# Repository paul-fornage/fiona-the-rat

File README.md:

### Fiona

# WIP
Only public to save progress at the expense of microsoft

KiCad Repo

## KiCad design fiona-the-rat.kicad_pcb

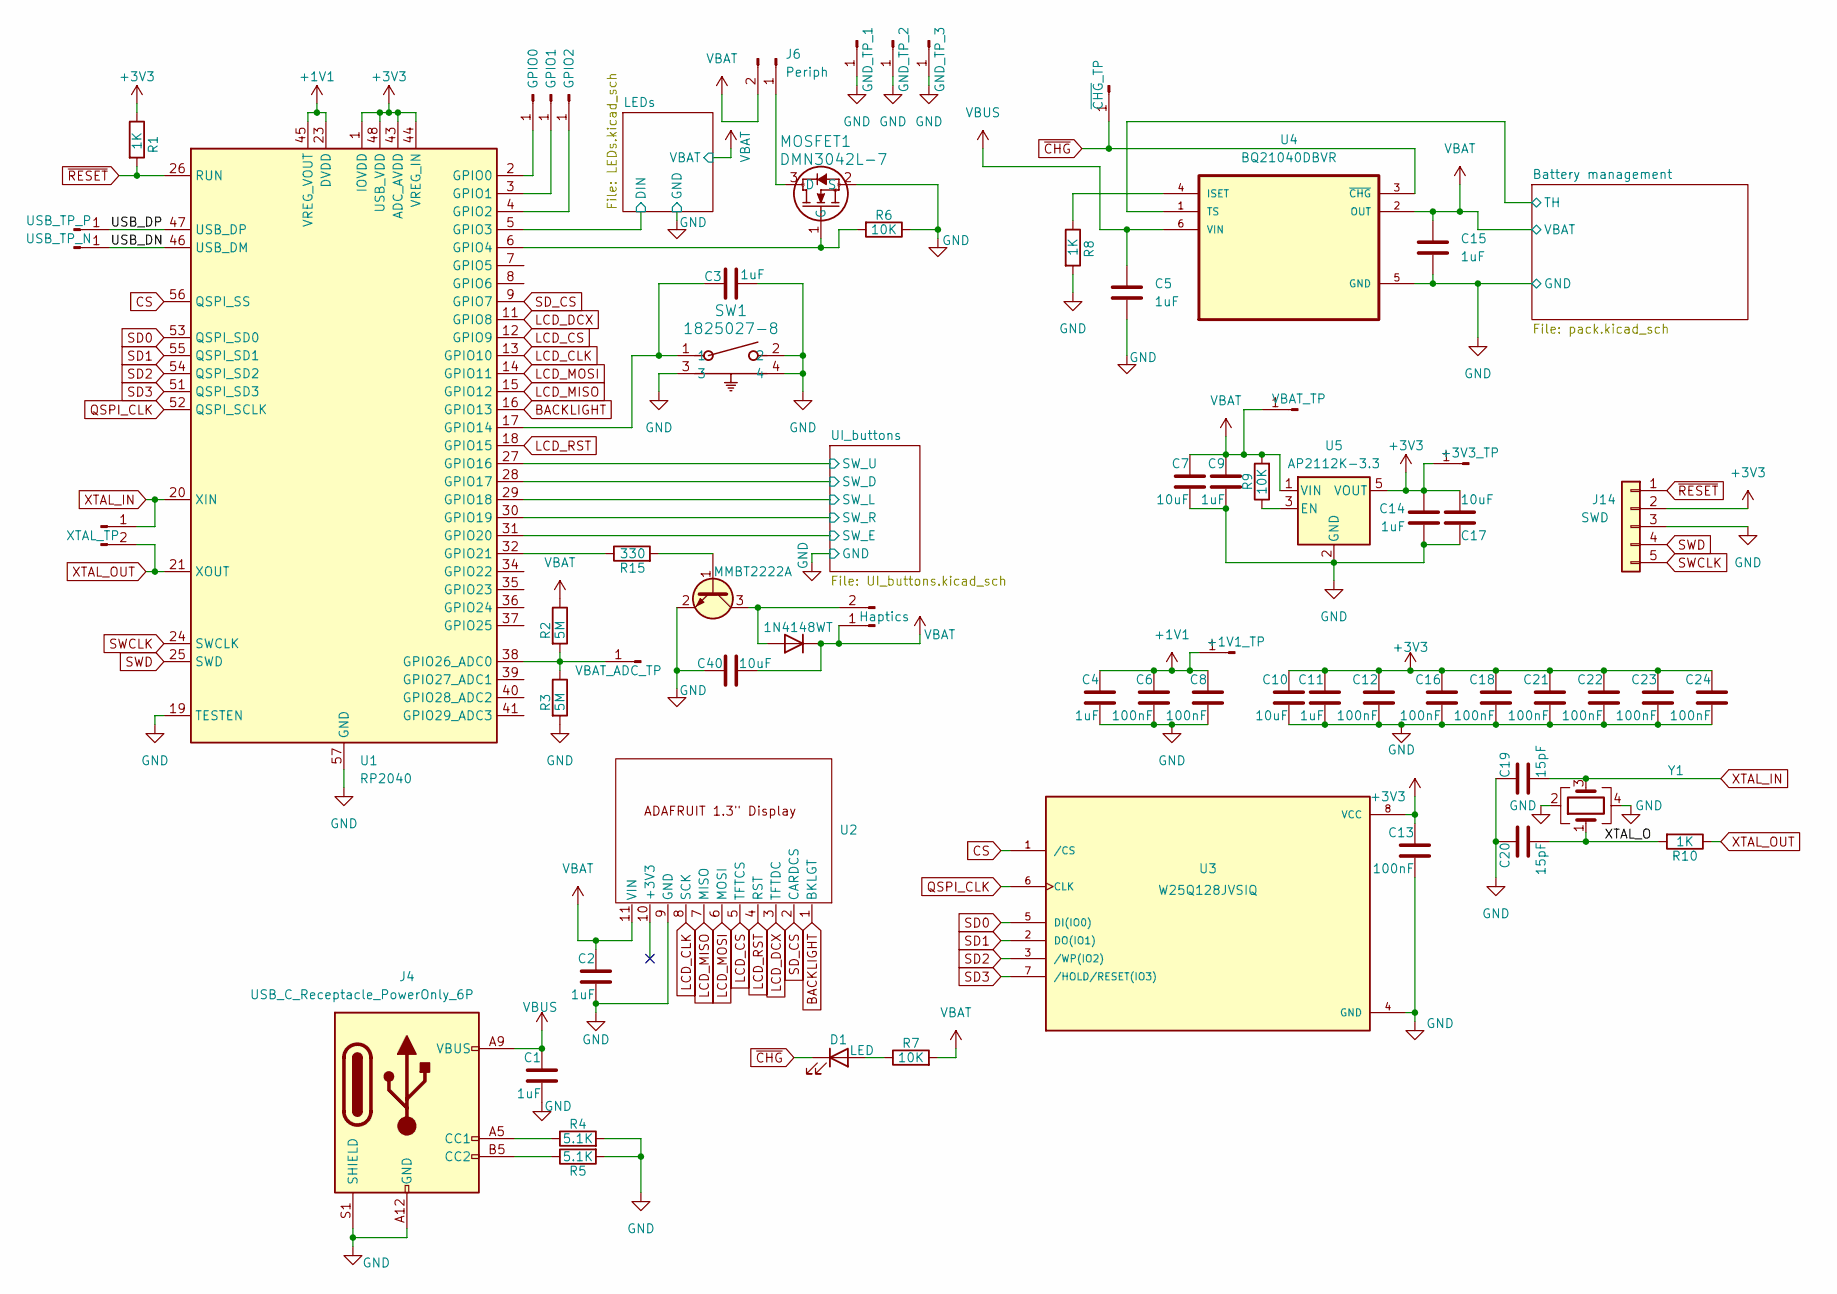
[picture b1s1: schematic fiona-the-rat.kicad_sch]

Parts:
C1, C2, C3, C4, C5, C9, C11, C14, C15: 1uF; C_0603_1608Metric
C6, C8, C12, C13, C16, C18, C21, C22, C23, C24: 100nF; C_0603_1608Metric
C7, C10, C17, C40: 10uF; C_0603_1608Metric
C19, C20: 15pF; C_0603_1608Metric
D1: LED; LED_0603_1608Metric
D2: 1N4148WT; D_SOD-523
J1: USB_TP_P; PinHeader_1x01_P2.54mm_Vertical
J2: USB_TP_N; PinHeader_1x01_P2.54mm_Vertical
J3: XTAL_TP; PinSocket_1x02_P2.54mm_Vertical
J4: USB_C_Receptacle_PowerOnly_6P; USB_C_Receptacle_GCT_USB4125-xx-x_6P_TopMnt_Horizontal
J5: VBAT_ADC_TP; PinHeader_1x01_P2.54mm_Vertical
J6: Periph; JST_XH_B2B-XH-A_1x02_P2.50mm_Vertical
J7: GND_TP_1; PinHeader_1x01_P2.54mm_Vertical
J8: GND_TP_2; PinHeader_1x01_P2.54mm_Vertical
J9: GND_TP_3; PinHeader_1x01_P2.54mm_Vertical
J10: ~{CHG}_TP; PinHeader_1x01_P2.54mm_Vertical
J11: +1V1_TP; PinHeader_1x01_P2.54mm_Vertical
J12: VBAT_TP; PinHeader_1x01_P2.54mm_Vertical
J13: +3V3_TP; PinHeader_1x01_P2.54mm_Vertical
J14: SWD; PinSocket_1x05_P2.54mm_Vertical
J19: GPIO0; PinHeader_1x01_P2.54mm_Vertical
J20: GPIO1; PinHeader_1x01_P2.54mm_Vertical
J21: GPIO2; PinHeader_1x01_P2.54mm_Vertical
J22: Haptics; JST_XH_B2B-XH-A_1x02_P2.50mm_Vertical
MOSFET1: DMN3042L-7; SOT23_DMN3042L_DIO
Q1: MMBT2222A; SOT-23
R1, R8, R10: 1K; R_0603_1608Metric
R2, R3: 5M; R_0603_1608Metric
R4, R5: 5.1K; R_0603_1608Metric
R6, R7, R9: 10K; R_0603_1608Metric
R15: 330; R_0603_1608Metric
SW1: 1825027-8; SW2_1825027-C_TEC
U1: RP2040; QFN-56-1EP_7x7mm_P0.4mm_EP3.2x3.2mm
U2: adafruit-4313-display
U3: W25Q128JVSIQ; SOIC127P790X216-8N; PARTREV I
U4: BQ21040DBVR; SOT95P280X145-6N
U5: AP2112K-3.3; SOT-23-5
Y1: Crystal_GND24; Crystal_SMD_Abracon_ABM8G-4Pin_3.2x2.5mm

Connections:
+1V1: C4.1, C6.1, C8.1, J11.1, U1.23 (DVDD), U1.45 (VREG_VOUT), U1.50 (DVDD)
+3V3: C10.1, C11.1, C12.1, C13.1, C14.1, C16.1, C17.2, C18.1, C21.1, C22.1, C23.1, C24.1, J13.1, J14.2, R1.1, U1.1 (IOVDD), U1.10 (IOVDD), U1.22 (IOVDD), U1.33 (IOVDD), U1.42 (IOVDD), U1.43 (ADC_AVDD), U1.44 (VREG_IN), U1.48 (USB_VDD), U1.49 (IOVDD), U3.8 (VCC), U5.5 (VOUT)
/Battery management/TH: U4.1 (TS); also elsewhere on the board
/LEDs/DIN: U1.5 (GPIO3); also elsewhere on the board
/UI_buttons/SW_D: U1.28 (GPIO17); also elsewhere on the board
/UI_buttons/SW_E: U1.31 (GPIO20); also elsewhere on the board
/UI_buttons/SW_L: U1.29 (GPIO18); also elsewhere on the board
/UI_buttons/SW_R: U1.30 (GPIO19); also elsewhere on the board
/UI_buttons/SW_U: U1.27 (GPIO16); also elsewhere on the board
/USB_DN: J2.1, U1.46 (USB_DM)
/USB_DP: J1.1, U1.47 (USB_DP)
/XTAL_O: C20.2, R10.2, Y1.1; also elsewhere on the board
BACKLIGHT: U1.16 (GPIO13), U2.1 (BKLGT)
CS: U1.56 (QSPI_SS), U3.1 (/CS)
GND: C1.2, C2.2, C3.2, C4.2, C5.2, C6.2, C7.2, C8.2, C9.2, C10.2, C11.2, C12.2, C13.2, C14.2, C15.2, C16.2, C17.1, C18.2, C19.1, C20.1, C21.2, C22.2, C23.2, C24.2, C40.1, J4.A12 (GND), J4.B12 (GND), J4.S1 (SHIELD), J7.1, J8.1, J9.1, J14.3, MOSFET1.2 (S), Q1.2 (E), R3.2, R4.2, R5.2, R6.1, R8.2, SW1.2, SW1.3, SW1.4, U1.19 (TESTEN), U1.57 (GND), U2.9 (GND), U3.4 (GND), U4.5 (GND), U5.2 (GND), Y1.2, Y1.4; also elsewhere on the board
LCD_CLK: U1.13 (GPIO10), U2.8 (SCK)
LCD_CS: U1.12 (GPIO9), U2.5 (TFTCS)
LCD_DCX: U1.11 (GPIO8), U2.3 (TFTDC)
LCD_MISO: U1.15 (GPIO12), U2.7 (MISO)
LCD_MOSI: U1.14 (GPIO11), U2.6 (MOSI)
LCD_RST: U1.18 (GPIO15), U2.4 (RST)
unnamed: D1.2 (A), R7.1
unnamed: D2.2 (A), J22.2, Q1.3 (C)
unnamed: J4.A5 (CC1), R4.1
unnamed: J4.B5 (CC2), R5.1
unnamed: J5.1, R2.2, R3.1, U1.38 (GPIO26_ADC0)
unnamed: J6.1, MOSFET1.3 (D)
unnamed: J19.1, U1.2 (GPIO0)
unnamed: J20.1, U1.3 (GPIO1)
unnamed: J21.1, U1.4 (GPIO2)
unnamed: MOSFET1.1 (G), R6.2, U1.6 (GPIO4)
unnamed: Q1.1 (B), R15.2
unnamed: C3.1, SW1.1, U1.17 (GPIO14)
unnamed: R15.1, U1.32 (GPIO21)
unnamed: R8.1, U4.4 (ISET)
unnamed: R9.1, U5.3 (EN)
QSPI_CLK: U1.52 (QSPI_SCLK), U3.6 (CLK)
SD0: U1.53 (QSPI_SD0), U3.5 (DI(IO0))
SD1: U1.55 (QSPI_SD1), U3.2 (DO(IO1))
SD2: U1.54 (QSPI_SD2), U3.3 (/WP(IO2))
SD3: U1.51 (QSPI_SD3), U3.7 (/HOLD/RESET(IO3))
SD_CS: U1.9 (GPIO7), U2.2 (CARDCS)
SWCLK: J14.5, U1.24 (SWCLK)
SWD: J14.4, U1.25 (SWD)
VBAT: C2.1, C7.1, C9.1, C15.1, C40.2, D2.1 (K), J6.2, J12.1, J22.1, R2.1, R7.2, R9.2, U2.11 (VIN), U4.2 (OUT), U5.1 (VIN); also elsewhere on the board
VBUS: C1.1, C5.1, J4.A9 (VBUS), J4.B9 (VBUS), U4.6 (VIN)
XTAL_IN: C19.2, J3.1, U1.20 (XIN), Y1.3; also elsewhere on the board
XTAL_OUT: J3.2, R10.1, U1.21 (XOUT)
~CHG: D1.1 (K), J10.1, U4.3 (~CHG)
~RESET: J14.1, R1.2, U1.26 (RUN)

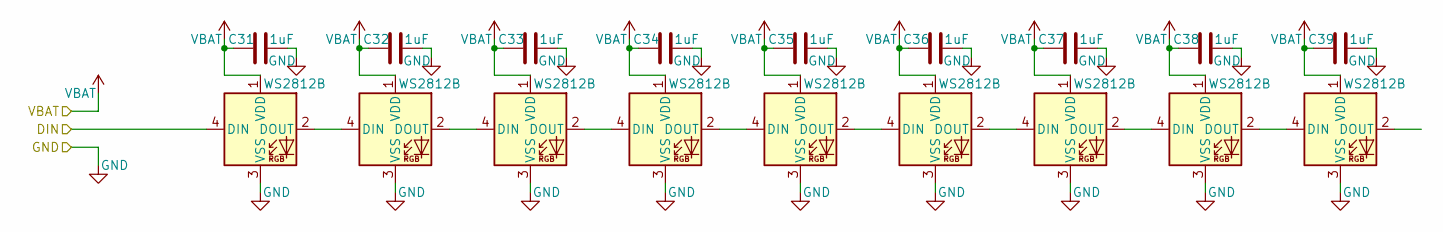
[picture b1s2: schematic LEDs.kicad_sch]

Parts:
C31, C32, C33, C34, C35, C36, C37, C38, C39: 1uF; C_0603_1608Metric
WLED1, WLED2, WLED3, WLED4, WLED5, WLED6, WLED7, WLED8, WLED9: WS2812B; LED_WS2812B_PLCC4_5.0x5.0mm_P3.2mm

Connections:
/LEDs/DIN: WLED1.4 (DIN); also elsewhere on the board
GND: C31.2, C32.2, C33.2, C34.2, C35.2, C36.2, C37.2, C38.2, C39.2, WLED1.3 (VSS), WLED2.3 (VSS), WLED3.3 (VSS), WLED4.3 (VSS), WLED5.3 (VSS), WLED6.3 (VSS), WLED7.3 (VSS), WLED8.3 (VSS), WLED9.3 (VSS); also elsewhere on the board
unnamed: WLED1.2 (DOUT), WLED2.4 (DIN)
unnamed: WLED2.2 (DOUT), WLED3.4 (DIN)
unnamed: WLED3.2 (DOUT), WLED4.4 (DIN)
unnamed: WLED4.2 (DOUT), WLED5.4 (DIN)
unnamed: WLED5.2 (DOUT), WLED6.4 (DIN)
unnamed: WLED6.2 (DOUT), WLED7.4 (DIN)
unnamed: WLED7.2 (DOUT), WLED8.4 (DIN)
unnamed: WLED8.2 (DOUT), WLED9.4 (DIN)
VBAT: C31.1, C32.1, C33.1, C34.1, C35.1, C36.1, C37.1, C38.1, C39.1, WLED1.1 (VDD), WLED2.1 (VDD), WLED3.1 (VDD), WLED4.1 (VDD), WLED5.1 (VDD), WLED6.1 (VDD), WLED7.1 (VDD), WLED8.1 (VDD), WLED9.1 (VDD); also elsewhere on the board

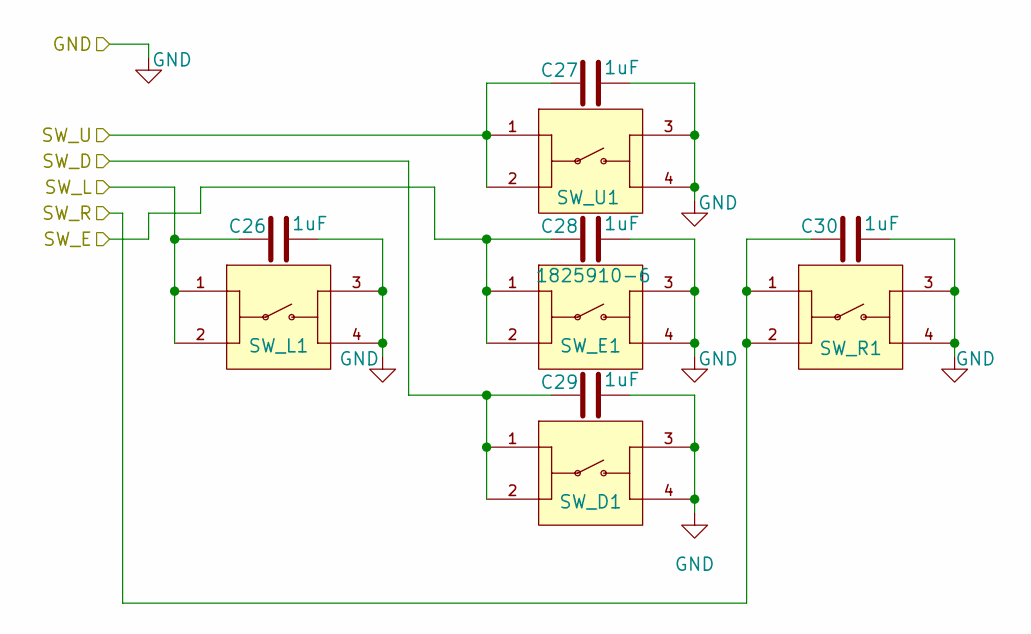
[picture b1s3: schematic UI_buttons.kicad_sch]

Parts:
C26, C27, C28, C29, C30: 1uF; C_0603_1608Metric
SW_D1: 1825910-6; SW_1825910-6-4; PARTREV C10
SW_E1: 1825910-6; SW_1825910-6-4; PARTREV C10
SW_L1: 1825910-6; SW_1825910-6-4; PARTREV C10
SW_R1: 1825910-6; SW_1825910-6-4; PARTREV C10
SW_U1: 1825910-6; SW_1825910-6-4; PARTREV C10

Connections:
/UI_buttons/SW_D: C29.1, SW_D1.1, SW_D1.2; also elsewhere on the board
/UI_buttons/SW_E: C28.1, SW_E1.1, SW_E1.2; also elsewhere on the board
/UI_buttons/SW_L: C26.1, SW_L1.1, SW_L1.2; also elsewhere on the board
/UI_buttons/SW_R: C30.1, SW_R1.1, SW_R1.2; also elsewhere on the board
/UI_buttons/SW_U: C27.1, SW_U1.1, SW_U1.2; also elsewhere on the board
GND: C26.2, C27.2, C28.2, C29.2, C30.2, SW_D1.3, SW_D1.4, SW_E1.3, SW_E1.4, SW_L1.3, SW_L1.4, SW_R1.3, SW_R1.4, SW_U1.3, SW_U1.4; also elsewhere on the board

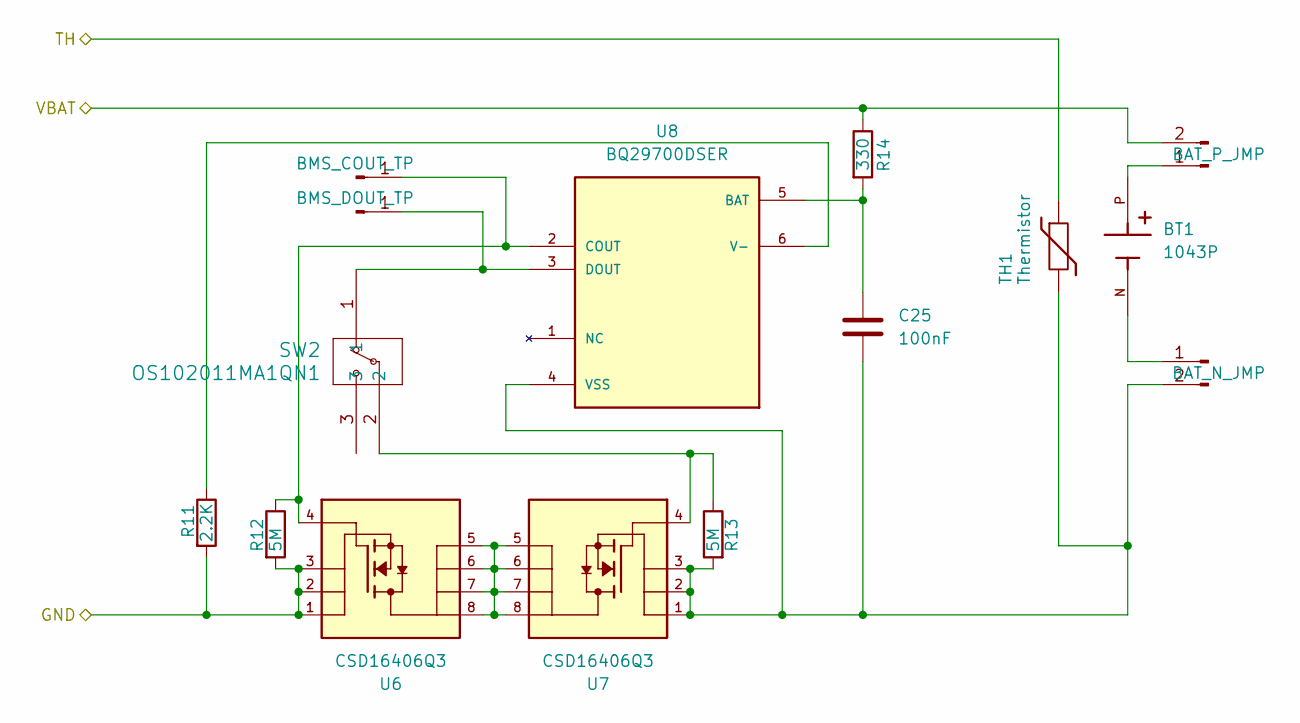
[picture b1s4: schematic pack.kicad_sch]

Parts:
BT1: 1043P; BAT_1043P; PARTREV D
C25: 100nF; C_0603_1608Metric
J15: BMS_COUT_TP; PinHeader_1x01_P2.54mm_Vertical
J16: BMS_DOUT_TP; PinHeader_1x01_P2.54mm_Vertical
J17: BAT_P_JMP; PinSocket_1x02_P2.54mm_Vertical
J18: BAT_N_JMP; PinSocket_1x02_P2.54mm_Vertical
R11: 2.2K; R_0603_1608Metric
R12, R13: 5M; R_0603_1608Metric
R14: 330; R_0603_1608Metric
SW2: OS102011MA1QN1; OS102011MA1QN1_CNK
TH1: Thermistor; R_0402_1005Metric
U6, U7: CSD16406Q3; TRANS_CSD16406Q3
U8: BQ29700DSER; SON50P150X150X80-6N; PARTREV G

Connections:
/Battery management/TH: TH1.1; also elsewhere on the board
GND: R11.2, R12.2, U6.1, U6.2, U6.3; also elsewhere on the board
unnamed: J15.1, R12.1, U6.4, U8.2 (COUT)
unnamed: J16.1, SW2.1, U8.3 (DOUT)
unnamed: BT1.P, J17.1
unnamed: BT1.N, J18.1
unnamed: C25.1, J18.2, R13.2, TH1.2, U7.1, U7.2, U7.3, U8.4 (VSS)
unnamed: R13.1, SW2.2, U7.4
unnamed: U6.5, U6.6, U6.7, U6.8, U7.5, U7.6, U7.7, U7.8
unnamed: C25.2, R14.2, U8.5 (BAT)
unnamed: R11.1, U8.6 (V-)
VBAT: J17.2, R14.1; also elsewhere on the board

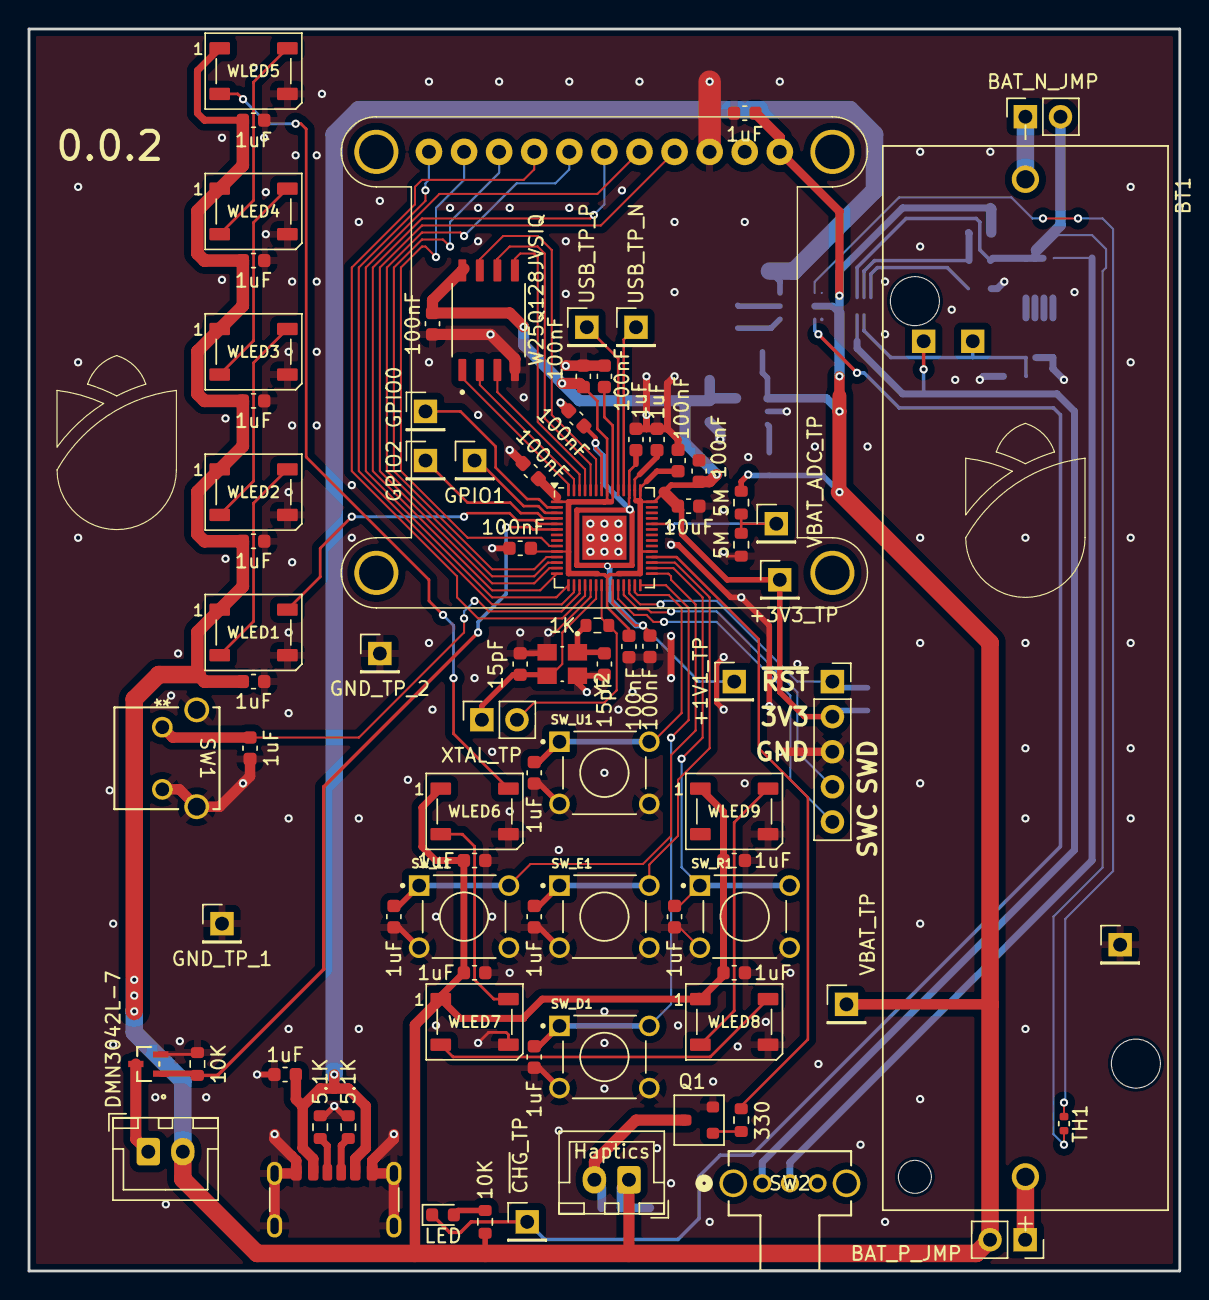
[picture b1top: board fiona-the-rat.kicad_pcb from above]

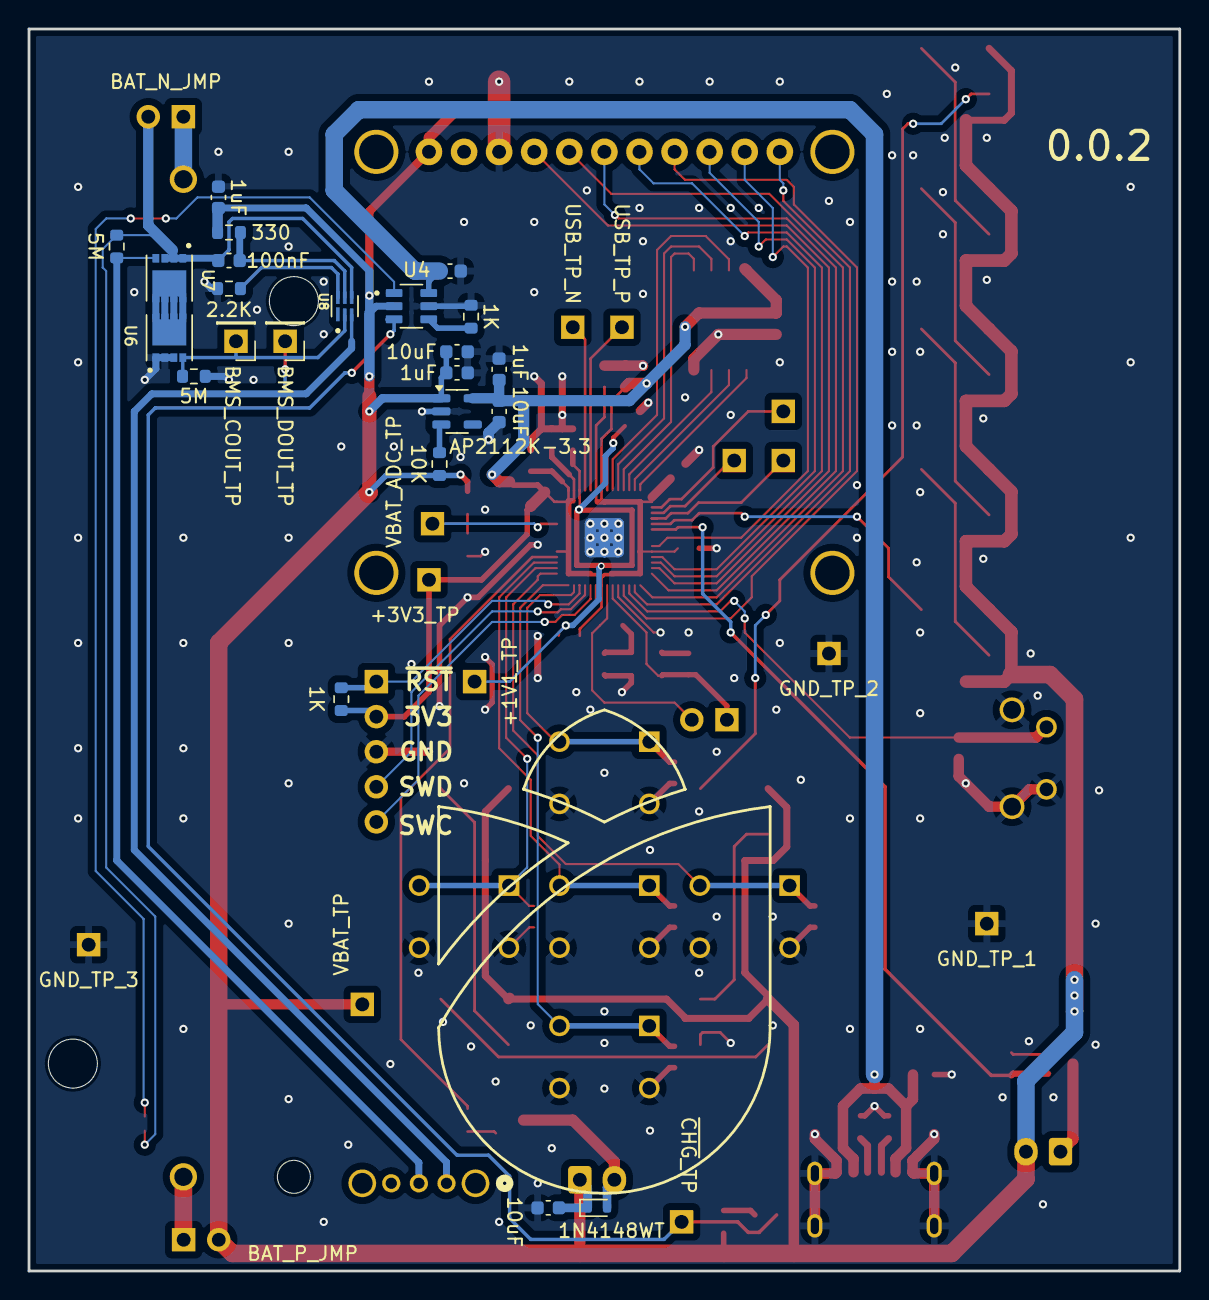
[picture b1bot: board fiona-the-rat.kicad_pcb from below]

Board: 2 copper layers, 83.3 x 89.9 mm, 108 parts (23 on the bottom side), 67 nets.

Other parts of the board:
Y2: ABM8G-12.000MHZ-18-D2Y-T; XTAL_ABM8G-12.000MHZ-18-D2Y-T

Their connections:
/XTAL_O: Y2.1; also elsewhere on the board
GND: Y2.2 (GND), Y2.4 (GND); also elsewhere on the board
XTAL_IN: Y2.3; also elsewhere on the board

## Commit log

2025-07-10 init
    just saving work, not finished
2025-07-10 working on stuff
2025-07-11 Forgor MD
2025-07-11 placed all components
2025-07-11 adding stuff
2025-07-11 tweaking
2025-07-11 0.0.1 test
2025-07-14 more lights
2025-07-14 Update fiona-the-rat.kicad_pcb
    add 0.0.2 text
2025-07-14 changed lib to owned
2025-07-14 change lib to owned
2025-07-14 I forgor
2025-07-15 swap 3v3 caps on rp2040
2025-07-15 breakout GPIO[0..=2]
2025-07-15 add haptic motor
2025-07-22 Flipped display pin ordering
    :/
2025-07-28 DRC fixes, swapped cryst lib
2025-07-28 swap crystal lib
2025-07-28 add DRC exclusions
    For keepout things in the ada4313 display mounting holes
2025-07-31 Add curr. sense to scheme
